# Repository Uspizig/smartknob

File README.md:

# smartknob
a BLDC Motor controller with the TMC6300 Driver and MT6701 magnetic encoder

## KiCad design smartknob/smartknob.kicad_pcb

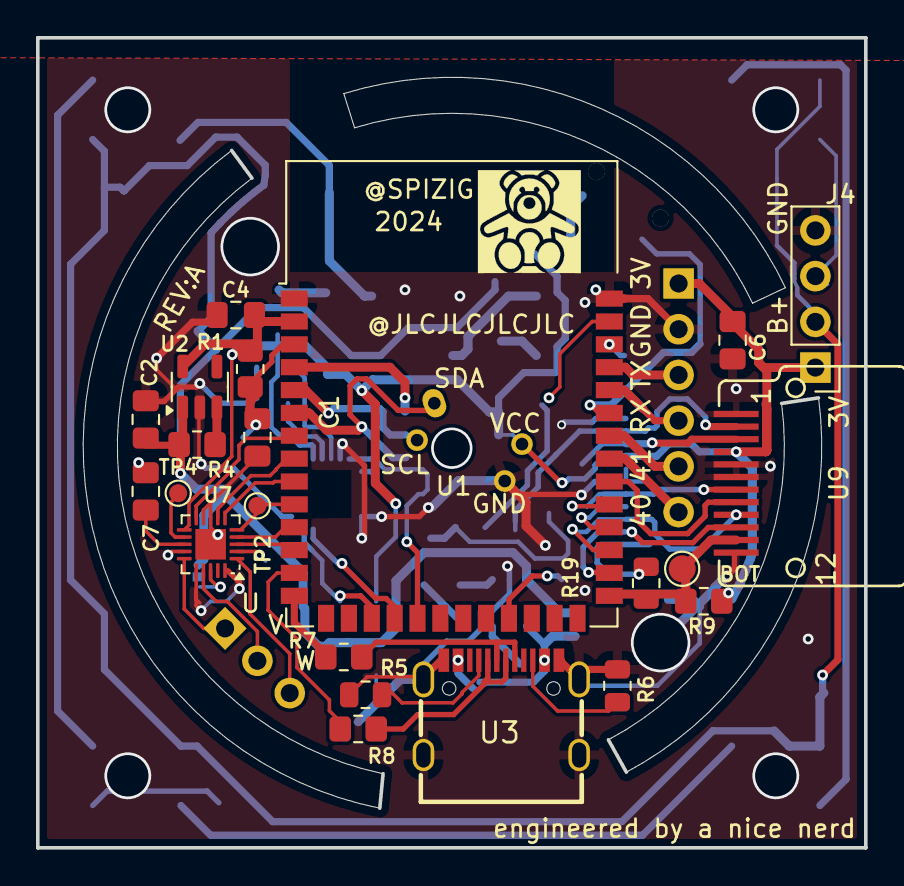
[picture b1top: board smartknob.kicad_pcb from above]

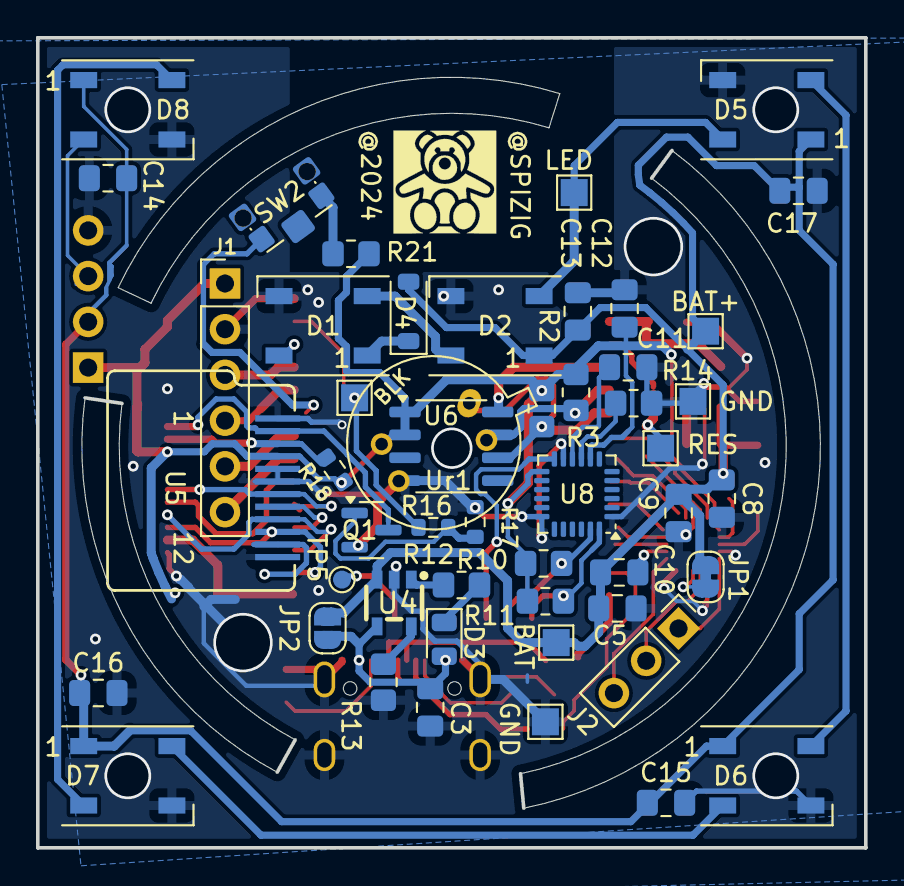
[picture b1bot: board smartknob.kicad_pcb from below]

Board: 2 copper layers, 46.0 x 45.0 mm, 74 parts (51 on the bottom side), 62 nets.

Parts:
BAT: TestPoint; TestPoint_Pad_1.5x1.5mm
BAT+: TestPoint; TestPoint_Pad_1.5x1.5mm
BLK: TestPoint; TestPoint_Pad_1.5x1.5mm
BOT: TestPoint; TestPoint_Pad_D1.5mm
C1, C3, C4, C5, C6, C7, C9, C11, C12, C13, C14, C15, C16, C17: 100nF; C_0805_2012Metric_Pad1.18x1.45mm_HandSolder
C2: 4.7uF50V; C_0805_2012Metric_Pad1.18x1.45mm_HandSolder
C8, C10: 22uF; C_0805_2012Metric_Pad1.18x1.45mm_HandSolder
D1, D2, D5, D6, D7, D8: WS2812B; LED_WS2812B_PLCC4_5.0x5.0mm_P3.2mm
D3: LED; LED_0805_2012Metric
D4: MBR0530; D_SOD-123
GND: TestPoint; TestPoint_Pad_1.5x1.5mm
GND#2: TestPoint; TestPoint_Pad_1.5x1.5mm
J1: Conn_01x06_Female; PinHeader_1x06_P2.54mm_Vertical
J2: Conn_01x03_Pin; PinHeader_1x03_P2.54mm_Vertical
J4: Conn_01x04_Pin; PinHeader_1x04_P2.54mm_Vertical
JP1: Jumper_2_Open; SolderJumper-2_P1.3mm_Bridged_RoundedPad1.0x1.5mm
JP2: Jumper_2_Open; SolderJumper-2_P1.3mm_Open_RoundedPad1.0x1.5mm
LED: TestPoint; TestPoint_Pad_1.5x1.5mm
Q1: 2N7002; SOT-23
R1, R9: 10K; R_0805_2012Metric_Pad1.20x1.40mm_HandSolder
R2, R3, R4, R10, R11, R14: 10k; R_0805_2012Metric_Pad1.20x1.40mm_HandSolder
R5, R6: 5k11; R_0805_2012Metric
R7, R8: 0R; R_0805_2012Metric_Pad1.20x1.40mm_HandSolder
R12, R13: 1K; R_0805_2012Metric_Pad1.20x1.40mm_HandSolder
R16: 10k; R_0603_1608Metric
R17: 1M; R_0603_1608Metric
R18: 22; R_0603_1608Metric
R19: 0R; R_0805_2012Metric
R21: 100K; R_0805_2012Metric_Pad1.20x1.40mm_HandSolder
RES: TestPoint; TestPoint_Pad_1.5x1.5mm
SW2: SW_Push; SW_SPST_CK_KMS2xxGP
TP1, TP3: BaerLogo; baerklein
TP2, TP4, TP5: TestPoint; TestPoint_Pad_D1.0mm
U1: ESP32-S3-WROOM-1-Espressif; ESP32-S3-WROOM-1
U2: RT9013; SOT-23-5
U3: KoreanHropartsElecTYPE-C-31-M-12; USB-C_SMD-TYPE-C-31-M-12
U4: TP4065; SOT-23-5_L3.0-W1.7-P0.95-LS2.8-BR
U5: GC9A01_IPS_display
U6: MT6701CT; SO-8_3.9x4.9mm_P1.27mm
U7: WQFN-20-1EP_3x3mm_P0.4mm_EP1.7x1.7mm
U8: MPU-6050; InvenSense_QFN-24_4x4mm_P0.5mm
U9: GC9A01_IPS_display; GC9A01_IPS_display_reversed
Ur1: MLX90640

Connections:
+3.3VP: C4.2, C6.2, C12.1, J1.1, J4.1, R1.2, R2.1, R3.1, R9.2, R10.1, R11.1, R18.1, R21.1, U1.2 (3V3), U2.5 (VOUT), U5.4 (VDD), U6.1 (VDD), U6.2 (MODE), U7.11 (VIO), U8.8 (VLOGIC), U8.13 (VDD), U9.4 (VDD), Ur1.2 (VDD)
+5VD: C3.1, D3.2 (A), JP2.1 (A), U3.A4 (VBUS), U3.A9 (VBUS), U3.B4 (VBUS), U3.B9 (VBUS), U4.4 (VCC)
+BATT: BAT.1, BAT+.1, C2.2, C5.2, C8.1, C9.1, C10.2, C13.1, C14.1, C15.1, C16.1, C17.1, D2.1 (VDD), D4.2 (A), D5.1 (VDD), D6.1 (VDD), D7.1 (VDD), D8.1 (VDD), J4.2, JP1.2 (B), JP2.2 (B), R4.2, U2.1 (VIN), U4.3 (BAT)
/BLDC_U: J2.1, U7.15 (U)
/BLDC_V: J2.2, U7.17 (V)
/BLDC_W: J2.3, U7.1 (W)
/BLK: BLK.1, R16.2, U1.39 (GPIO1/TOUCH1/ADC1_CH0)
/DN: R8.1, U3.A7 (DN1), U3.B7 (DN2)
/DP: R7.2, U3.A6 (DP1), U3.B6 (DP2)
/GPIO40: J1.6, U1.33 (MTDO/GPIO40/CLK_OUT2)
/GPIO41: J1.5, U1.34 (MTDI/GPIO41/CLK_OUT1)
/GPIO43: J1.3, U1.37 (U0TXD/GPIO43/CLK_OUT1)
/GPIO44: J1.4, U1.36 (U0RXD/GPIO44/CLK_OUT2)
/INT_MP6050: U1.19 (GPIO11/TOUCH11/ADC2_CH0/FSPICS0/FSPIIO4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), U8.12 (INT)
/LEDA: R18.2, U5.3 (LEDA), U9.3 (LEDA)
/LEDK: Q1.3 (D), U5.2 (LEDK), U9.2 (LEDK)
/LED_WS2812: D1.4 (DIN), U1.38 (GPIO2/TOUCH2/ADC1_CH1)
/MAG_CLK: R3.2, U1.5 (GPIO5/TOUCH5/ADC1_CH4), U6.7 (B), Ur1.4 (SCL)
/MAG_CSN: U1.4 (GPIO4/TOUCH4/ADC1_CH3), U6.8 (Z)
/MAG_DO: R2.2, U1.6 (GPIO6/TOUCH6/ADC1_CH5), U6.6 (A), Ur1.1 (SDA)
/MOSI: U1.28 (SPIIO6/GPIO35/FSPID/SUBSPID), U5.10 (SDI), U9.10 (SDI)
/SCK: U1.29 (SPIIO7/GPIO36/FSPICLK/SUBSPICLK), U5.9 (SCK), U9.9 (SCK)
/SCL: R10.2, U1.18 (GPIO10/TOUCH10/ADC1_CH9/FSPICS0/FSPIIO4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), U8.23 (SCL)
/SDA: R11.2, U1.17 (GPIO9/TOUCH9/ADC1_CH8/FSPIHD/SUBSPIHD), U8.24 (SDA)
/SW_X: SW2.2, U1.35 (MTMS/GPIO42)
/TFT2_CS: U1.32 (MTCK/GPIO39/CLK_OUT3/SUBSPICS1), U9.8 (~CS)
/TFT_CS: U1.30 (SPIDQS/GPIO37/FSPIQ/SUBSPIQ), U5.8 (~CS)
/TFT_DC: U1.31 (GPIO38/FSPIWP/SUBSPIWP), U5.7 (D/C), U9.7 (D/C)
/TFT_RST: BOT.1, R9.1, R19.2, U1.27 (GPIO0/BOOT), U9.11 (~RESET)
/TMC_DIAG: TP4.1, U7.12 (DIAG)
/TMC_UH: U1.12 (GPIO8/TOUCH8/ADC1_CH7/SUBSPICS1), U7.3 (UH)
/TMC_UL: U1.9 (GPIO16/U0CTS/ADC2_CH5/XTAL_32K_NH5), U7.6 (UL)
/TMC_VH: U1.11 (GPIO18/U1RXD/ADC2_CH7/CLK_OUT3), U7.4 (VH)
/TMC_VL: U1.7 (GPIO7/TOUCH7/ADC1_CH6), U7.10 (VL)
/TMC_WH: TP2.1, U1.10 (GPIO17/U1TXD/ADC2_CH6), U7.5 (WH)
/TMC_WL: U1.8 (GPIO15/U0RTS/ADC2_CH4/XTAL_32K_P), U7.7 (WL)
GND: C1.1, C2.1, C3.2, C4.1, C5.1, C6.1, C7.1, C8.2, C9.2, C11.1, C12.2, C13.2, C14.2, C15.2, C16.2, C17.2, D1.3 (VSS), D2.3 (VSS), D5.3 (VSS), D6.3 (VSS), D7.3 (VSS), D8.3 (VSS), GND.1, GND#2.1, J1.2, J4.4, Q1.2 (S), R5.1, R6.2, R13.2, R14.2, R17.1, U1.1 (GND), U1.40 (GND), U2.2 (GND), U3.0, U3.A1 (GND), U3.A12 (GND), U3.B1 (GND), U3.B12 (GND), U4.2 (GND), U5.1 (GND), U5.5 (GND), U5.6 (GND), U5.12 (GND), U6.4 (GND), U7.8 (GND), U7.9 (GND), U7.14 (GND), U7.16 (BRUV), U7.20 (BRW), U7.21 (EP), U8.1 (CLKIN), U8.11 (FSYNC), U8.18 (GND), U9.1 (GND), U9.5 (GND), U9.6 (GND), U9.12 (GND), Ur1.3 (GND)
unnamed: D1.2 (DOUT), D2.4 (DIN)
unnamed: D1.1 (VDD), D4.1 (K)
unnamed: D2.2 (DOUT), D5.4 (DIN), LED.1
unnamed: D3.1 (K), R12.1
unnamed: D5.2 (DOUT), D6.4 (DIN)
unnamed: D6.2 (DOUT), D7.4 (DIN)
unnamed: D7.2 (DOUT), D8.4 (DIN)
unnamed: D8.2 (DOUT), J4.3
unnamed: JP1.1 (A), U7.18 (VS)
unnamed: Q1.1 (G), R16.1, R17.2
unnamed: R21.2, SW2.1
unnamed: C1.2, R1.1, RES.1, U1.3 (EN)
unnamed: R8.2, U1.13 (GPIO19/U1RTS/ADC2_CH8/CLK_OUT2/USB_D-)
unnamed: R7.1, U1.14 (GPIO20/U1CTS/ADC2_CH9/CLK_OUT1/USB_D+)
unnamed: TP5.1, U1.23 (GPIO21)
unnamed: R4.1, U2.3 (EN)
unnamed: R5.2, U3.A5 (CC1)
unnamed: R6.1, U3.B5 (CC2)
unnamed: R12.2, U4.1 (CHRG)
unnamed: R13.1, U4.5 (PROG)
unnamed: R19.1, U5.11 (~RESET)
unnamed: C7.2, U7.13 (1.8VOUT)
unnamed: C10.1, U7.2 (VCP)
unnamed: R14.1, U8.9 (AD0)
unnamed: C11.2, U8.10 (REGOUT)
